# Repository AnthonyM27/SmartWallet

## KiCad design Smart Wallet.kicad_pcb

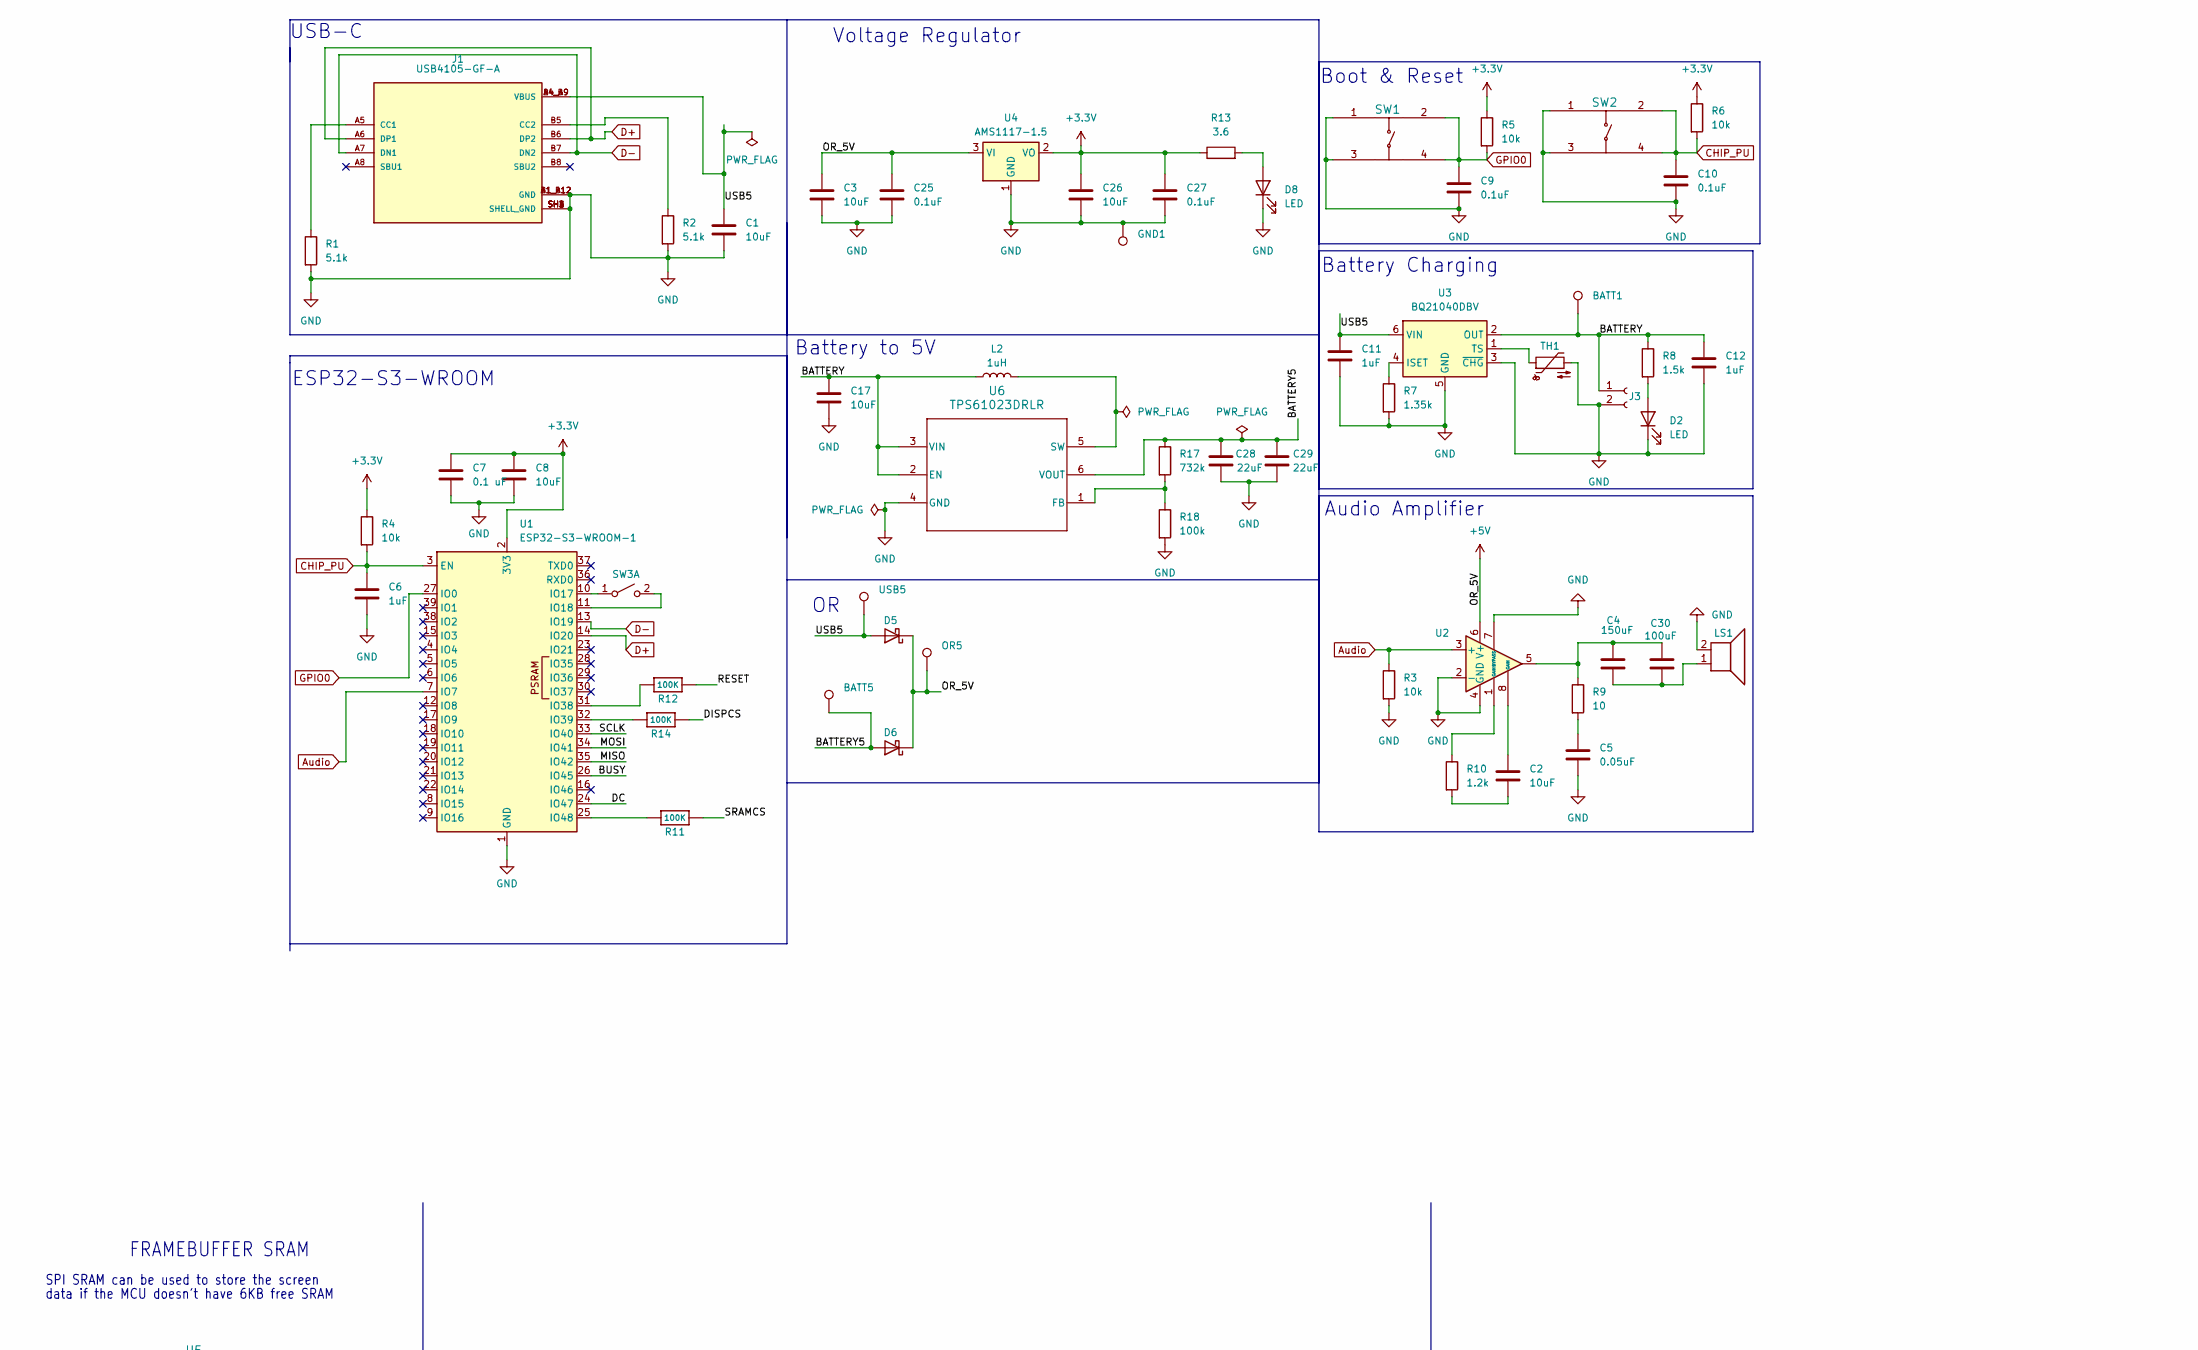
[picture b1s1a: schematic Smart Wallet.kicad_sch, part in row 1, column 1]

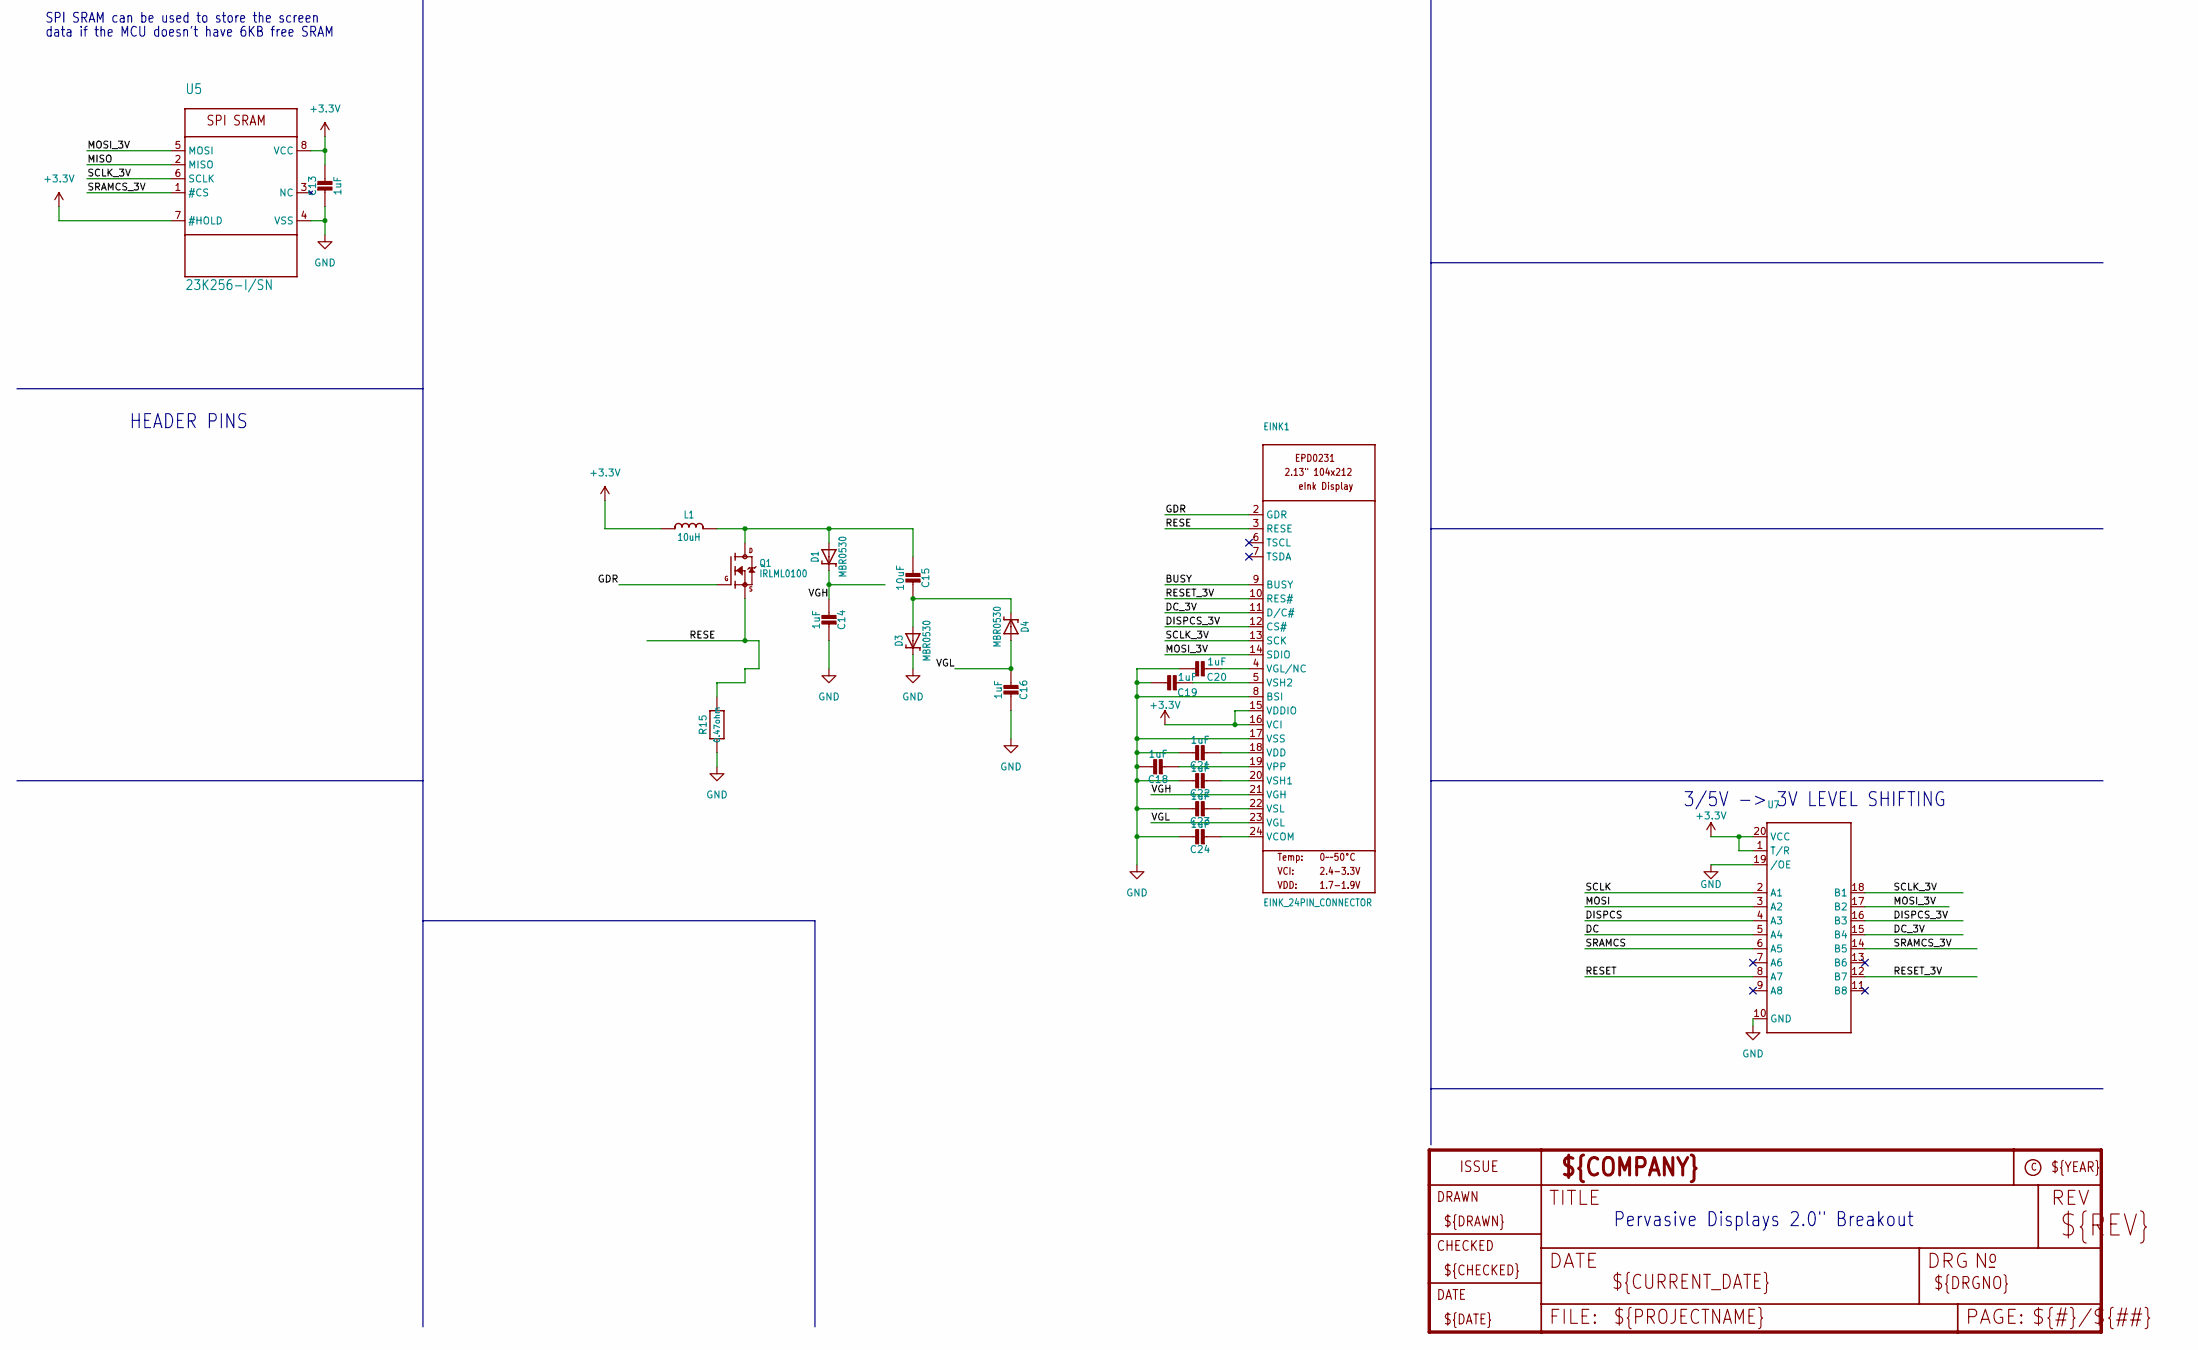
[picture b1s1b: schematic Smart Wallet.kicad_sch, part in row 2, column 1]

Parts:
BATT1, BATT5: TestPoint; MountingHole_2.5mm_Pad
C1, C2, C3, C8, C15, C17, C26: 10uF; C_0805_2012Metric
C4: 150uF; C_1210_3225Metric
C5: 0.05uF; C_0805_2012Metric
C6, C11, C12, C13, C14, C16, C18, C19, C20, C21, C22, C23, C24: 1uF; C_0805_2012Metric
C7: 0.1 uF; C_0805_2012Metric
C9, C10, C25, C27: 0.1uF; C_0805_2012Metric
C28, C29: 22uF; C_0805_2012Metric
C30: 100uF; C_0805_2012Metric
D1, D3, D4: MBR0530
D2, D8: LED; LED_0805_2012Metric
D5, D6: D_Schottky; D_SOD-128
EINK1: EINK_24PIN_CONNECTOR; EINK_24PIN
GND1: TestPoint; MountingHole_2.5mm_Pad
J1: USB4105-GF-A; USB4105-GF-A_GCT; PARTREV B3
J3: Conn_01x02_Socket; JST_SH_SM02B-SRSS-TB_1x02-1MP_P1.00mm_Horizontal
L1: 10uH; Inductor L1
L2: 1uH; L_0805_2012Metric
LS1: Speaker; CMS-151504 Speaker
OR5: TestPoint; MountingHole_2.5mm_Pad
Q1: IRLML0100; Q1 IRLML0100
R1, R2: 5.1k; R_0805_2012Metric
R3, R4, R5, R6: 10k; R_0805_2012Metric
R7: 1.35k; R_0603_1608Metric
R8: 1.5k; R_0805_2012Metric
R9: 10; R_0805_2012Metric
R10: 1.2k; R_0805_2012Metric
R11, R12, R14: 100K; R_0805_2012Metric
R13: 3.6; R_0805_2012Metric
R15: 0.47ohm; R_0805_2012Metric
R17: 732k; R_0805_2012Metric
R18: 100k; R_0805_2012Metric
SW1, SW2: PTS810 SJM 250 SMTR LFS; PTS810_CNK
SW3: SW_DPST_x2; MISM-7LR-6-10 REED
TH1: Thermistor_NTC; R_0805_2012Metric
U1: ESP32-S3-WROOM-1
U2: LM386
U3: BQ21040DBV; SOT-23-6
U4: AMS1117-1.5; SOT-223-3_TabPin2
U5: 23K256-I/SN; 23k256
U6: TPS61023DRLR; DRL0006A
U7: 74LCX245
USB5: TestPoint; MountingHole_2.5mm_Pad

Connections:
+3.3V: C7.1, C8.1, C13.1, C26.1, C27.1, EINK1.15 (VDDIO), EINK1.16 (VCI), L1.P$2 (2), R4.1, R5.1, R6.1, R13.1, U1.2 (3V3), U4.2 (VO), U5.7 (#HOLD), U5.8 (VCC), U7.1 (T/R), U7.20 (VCC)
+5V: C3.1, C25.1, D5.1 (K), D6.1 (K), OR5.1, U2.6 (V+), U4.3 (VI)
/BATTERY: BATT1.1, C12.1, C17.1, J3.1, L2.1, R8.1, U3.2 (OUT), U6.2 (EN), U6.3 (VIN)
/BATTERY5: BATT5.1, C28.1, C29.1, D6.2 (A), R17.1, U6.6 (VOUT)
/BUSY: EINK1.9 (BUSY), U1.26 (IO45)
/DC: U1.24 (IO47), U7.5 (A4)
/DC_3V: EINK1.11 (D/C#), U7.15 (B4)
/DISPCS: R14.1, U7.4 (A3)
/DISPCS_3V: EINK1.12 (CS#), U7.16 (B3)
/GDR: EINK1.2 (GDR), Q1.1 (G)
/MISO: U1.35 (IO42), U5.2 (MISO)
/MOSI: U1.34 (IO41), U7.3 (A2)
/MOSI_3V: EINK1.14 (SDIO), U5.5 (MOSI), U7.17 (B2)
/RESE: EINK1.3 (RESE), Q1.2 (S), R15.1
/RESET: R12.1, U7.8 (A7)
/RESET_3V: EINK1.10 (RES#), U7.12 (B7)
/SCLK: U1.33 (IO40), U7.2 (A1)
/SCLK_3V: EINK1.13 (SCK), U5.6 (SCLK), U7.18 (B1)
/SRAMCS: R11.1, U7.6 (A5)
/SRAMCS_3V: U5.1 (#CS), U7.14 (B5)
/USB5: C1.1, C11.1, D5.2 (A), J1.A4_B9 (VBUS), J1.B4_A9 (VBUS), U3.6 (VIN), USB5.1
/VGH: C14.1, D1.C, EINK1.21 (VGH)
/VGL: C16.1, D4.A, EINK1.23 (VGL)
Audio: R3.1, U1.7 (IO7), U2.3 (+)
CHIP_PU: C6.1, C10.1, R4.2, R6.2, SW2.2, SW2.4, U1.3 (EN)
D+: J1.A6 (DP1), J1.B6 (DP2), U1.14 (IO20)
D-: J1.A7 (DN1), J1.B7 (DN2), U1.13 (IO19)
GND: C1.2, C3.2, C5.2, C6.2, C7.2, C8.2, C9.2, C10.2, C11.2, C12.2, C13.2, C14.2, C16.2, C17.2, C18.1, C19.1, C20.1, C21.1, C22.1, C23.1, C24.1, C25.2, C26.2, C27.2, C28.2, C29.2, D2.1 (K), D3.C, D8.1 (K), EINK1.8 (BSI), EINK1.17 (VSS), GND1.1, J1.A1_B12 (GND), J1.B1_A12 (GND), J1.SH1 (SHELL_GND), J1.SH2 (SHELL_GND), J1.SH3 (SHELL_GND), J1.SH4 (SHELL_GND), J3.2, LS1.2, R1.2, R2.2, R3.2, R7.2, R15.2, R18.2, SW1.1, SW1.3, SW2.1, SW2.3, TH1.2, U1.1 (GND), U1.40 (GND), U1.41 (GND), U2.2 (-), U2.4 (GND), U2.7 (BYPASS), U3.3 (~CHG), U3.5 (GND), U4.1 (GND), U5.4 (VSS), U6.4 (GND), U7.10 (GND), U7.19 (/OE)
GPIO0: C9.1, R5.2, SW1.2, SW1.4, U1.27 (IO0)
unnamed: C2.1, U2.8 (GAIN)
unnamed: C2.2, R10.2
unnamed: C5.1, R9.2
unnamed: C15.2, D3.A, D4.C
unnamed: C4.2, C30.1, R9.1, U2.5
unnamed: C4.1, C30.2, LS1.1
unnamed: D2.2 (A), R8.2
unnamed: D8.2 (A), R13.2
unnamed: C24.2, EINK1.24 (VCOM)
unnamed: C21.2, EINK1.18 (VDD)
unnamed: C20.2, EINK1.4 (VGL/NC)
unnamed: C18.2, EINK1.19 (VPP)
unnamed: C22.2, EINK1.20 (VSH1)
unnamed: C19.2, EINK1.5 (VSH2)
unnamed: C23.2, EINK1.22 (VSL)
unnamed: J1.A5 (CC1), R1.1
unnamed: J1.B5 (CC2), R2.1
unnamed: C15.1, D1.A, L1.P$1 (1), Q1.3 (D)
unnamed: R10.1, U2.1 (GAIN)
unnamed: SW3.1 (A), U1.10 (IO17)
unnamed: SW3.2 (B), U1.11 (IO18)
unnamed: R12.2, U1.31 (IO38)
unnamed: R14.2, U1.32 (IO39)
unnamed: R11.2, U1.25 (IO48)
unnamed: R7.1, U3.4 (ISET)
unnamed: TH1.1, U3.1 (TS)
unnamed: R17.2, R18.1, U6.1 (FB)
unnamed: L2.2, U6.5 (SW)

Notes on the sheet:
Voltage Regulator
FRAMEBUFFER SRAM
Battery to 5V
Pervasive Displays 2.0" Breakout
SPI SRAM can be used to store the screen
HEADER PINS
Battery Charging
data if the MCU doesn't have 6KB free SRAM
ESP32-S3-WROOM
USB-C
Boot & Reset
Audio Amplifier
3/5V -> 3V LEVEL SHIFTING

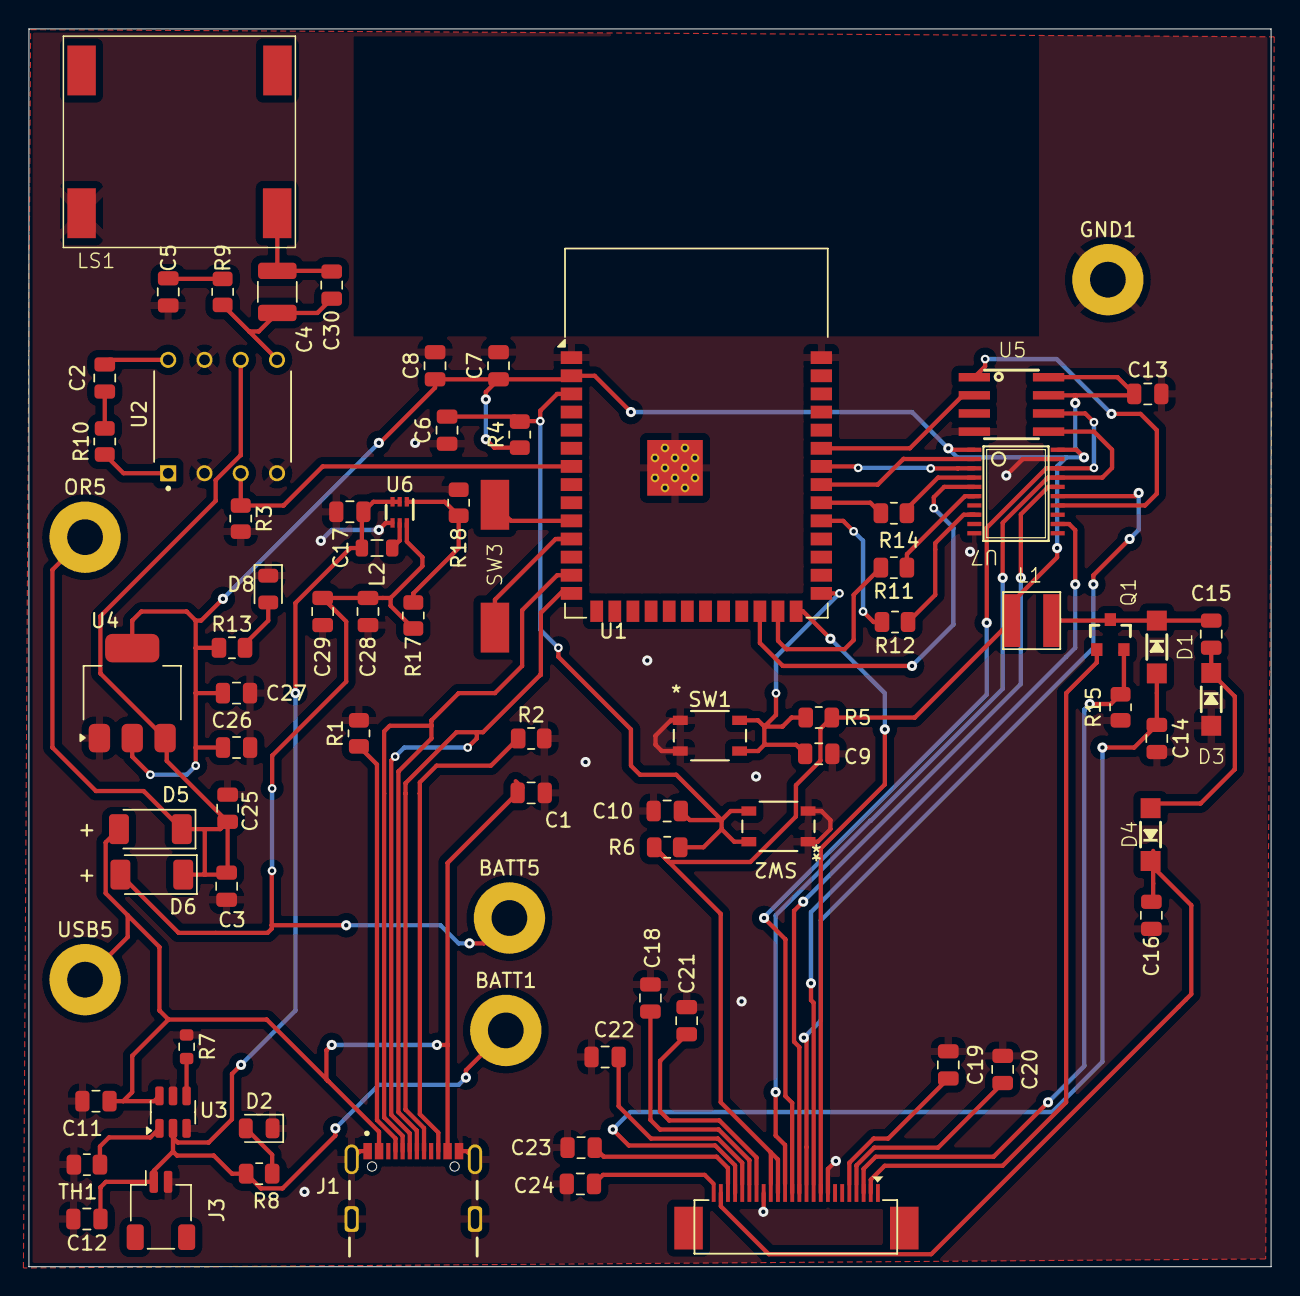
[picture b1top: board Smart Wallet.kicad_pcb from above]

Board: 2 copper layers, 87.0 x 86.7 mm, 77 parts (0 on the bottom side), 57 nets.
